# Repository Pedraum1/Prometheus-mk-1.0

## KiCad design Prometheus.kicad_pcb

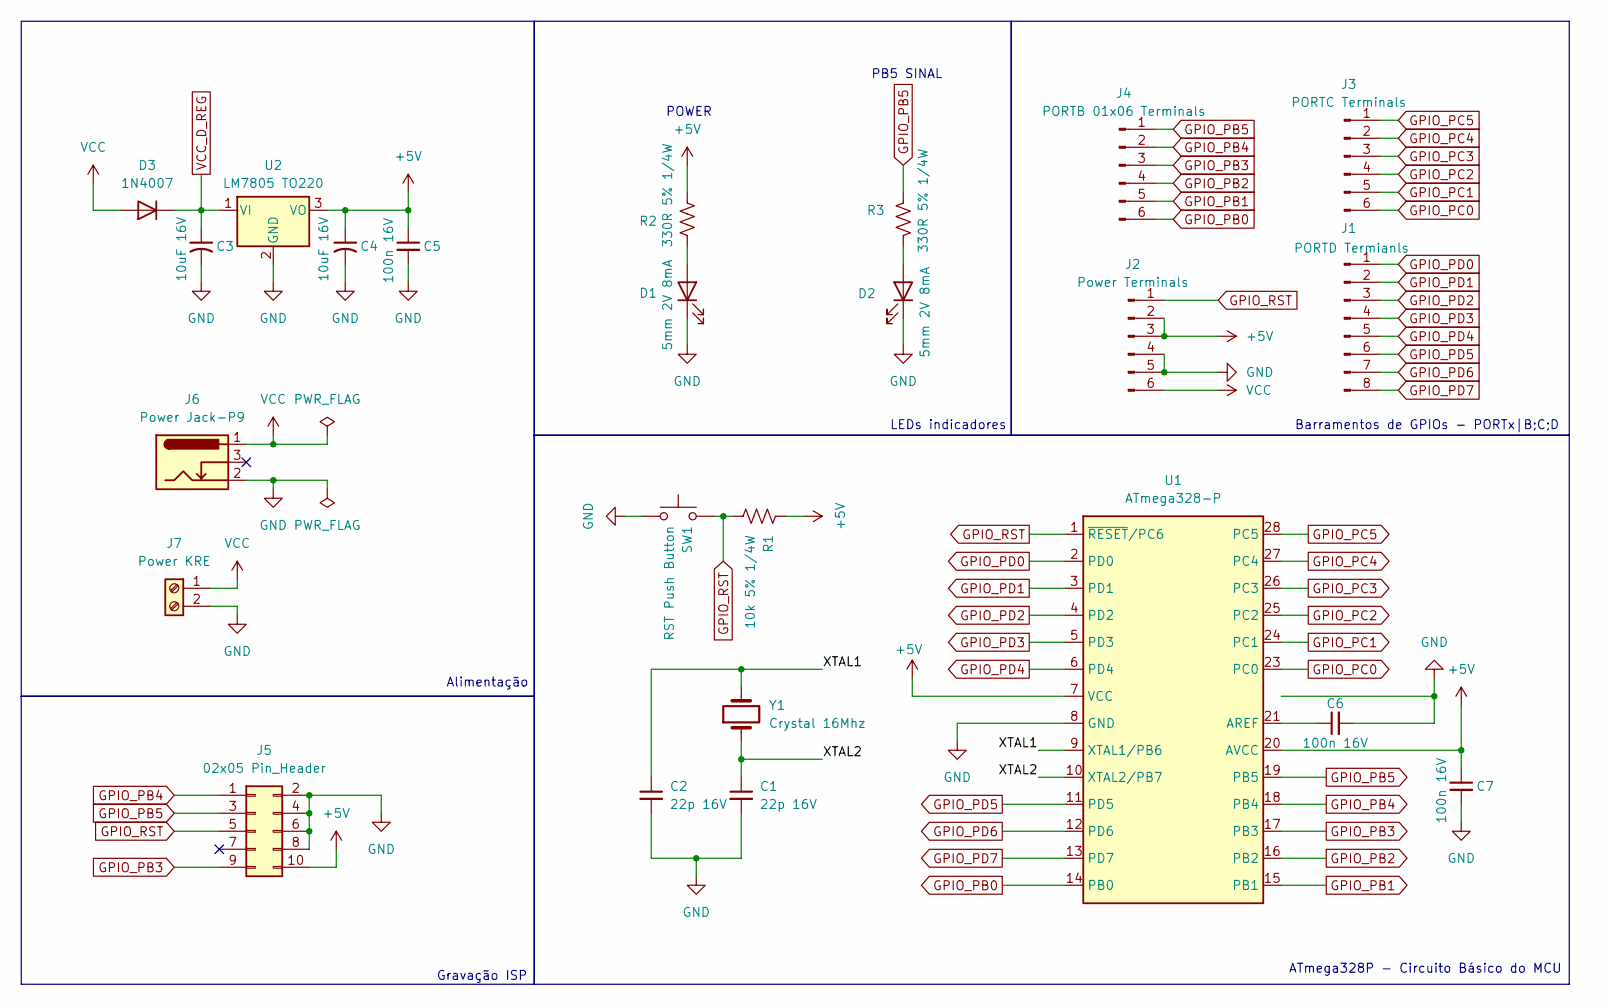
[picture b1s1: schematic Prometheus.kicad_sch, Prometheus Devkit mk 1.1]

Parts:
C1, C2: 22p 16V; C_Disc_D4.7mm_W2.5mm_P5.00mm
C3, C4: 10uF 16V; C_Radial_D5.0mm_H11.0mm_P2.00mm
C5, C6, C7: 100n 16V; C_Disc_D4.7mm_W2.5mm_P5.00mm
D1, D2: 5mm 2V 8mA; LED_D5.0mm
D3: 1N4007; D_DO-41_SOD81_P10.16mm_Horizontal
J1: PORTD Termianls; PinSocket_1x08_P2.54mm_Vertical
J2: Power Terminals; PinSocket_1x06_P2.54mm_Vertical
J3: PORTC Terminals; PinSocket_1x06_P2.54mm_Vertical
J4: PORTB 01x06 Terminals; PinSocket_1x06_P2.54mm_Vertical
J5: 02x05 Pin_Header; IDC-Header_2x05_P2.54mm_Vertical
J6: Power Jack-P9; BarrelJack_Horizontal
J7: Power KRE; TerminalBlock_Phoenix_MKDS-1,5-2-5.08_1x02_P5.08mm_Horizont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
R1: 10k 5% 1/4W; R_Axial_DIN0207_L6.3mm_D2.5mm_P7.62mm_Horizontal
R2, R3: 330R 5% 1/4W; R_Axial_DIN0207_L6.3mm_D2.5mm_P7.62mm_Horizontal
SW1: RST Push Button; SW_PUSH_6mm_H4.3mm
U1: ATmega328-P; DIP-28_W7.62mm_Socket
U2: LM7805 TO220; TO-220-3_Vertical
Y1: Crystal 16Mhz; Crystal_HC49-U_Vertical

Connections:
+5V: C4.1, C5.1, C7.1, J2.2, J2.3, J5.10, R1.1, R2.1, U1.7 (VCC), U1.20 (AVCC), U2.3 (VO)
/XTAL1: C2.1, U1.9 (XTAL1/PB6), Y1.2
/XTAL2: C1.1, U1.10 (XTAL2/PB7), Y1.1
GND: C1.2, C2.2, C3.2, C4.2, C5.2, C6.2, C7.2, D1.1 (K), D2.1 (K), J2.4, J2.5, J5.2, J5.4, J5.6, J5.8, J6.2, J7.2, SW1.1, U1.8 (GND), U1.22 (GND), U2.2 (GND)
GPIO_PB0: J4.6, U1.14 (PB0)
GPIO_PB1: J4.5, U1.15 (PB1)
GPIO_PB2: J4.4, U1.16 (PB2)
GPIO_PB3: J4.3, J5.9, U1.17 (PB3)
GPIO_PB4: J4.2, J5.1, U1.18 (PB4)
GPIO_PB5: J4.1, J5.3, R3.1, U1.19 (PB5)
GPIO_PC0: J3.6, U1.23 (PC0)
GPIO_PC1: J3.5, U1.24 (PC1)
GPIO_PC2: J3.4, U1.25 (PC2)
GPIO_PC3: J3.3, U1.26 (PC3)
GPIO_PC4: J3.2, U1.27 (PC4)
GPIO_PC5: J3.1, U1.28 (PC5)
GPIO_PD0: J1.1, U1.2 (PD0)
GPIO_PD1: J1.2, U1.3 (PD1)
GPIO_PD2: J1.3, U1.4 (PD2)
GPIO_PD3: J1.4, U1.5 (PD3)
GPIO_PD4: J1.5, U1.6 (PD4)
GPIO_PD5: J1.6, U1.11 (PD5)
GPIO_PD6: J1.7, U1.12 (PD6)
GPIO_PD7: J1.8, U1.13 (PD7)
GPIO_RST: J2.1, J5.5, R1.2, SW1.2, U1.1 (~RESET/PC6)
unnamed: D1.2 (A), R2.2
unnamed: D2.2 (A), R3.2
unnamed: C6.1, U1.21 (AREF)
VCC: D3.2 (A), J2.6, J6.1, J7.1
VCC_D_REG: C3.1, D3.1 (K), U2.1 (VI)

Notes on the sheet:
PB5 SINAL
LEDs indicadores
POWER
Alimentação
Gravação ISP
ATmega328P - Circuito Básico do MCU
Barramentos de GPIOs - PORTx|B;C;D

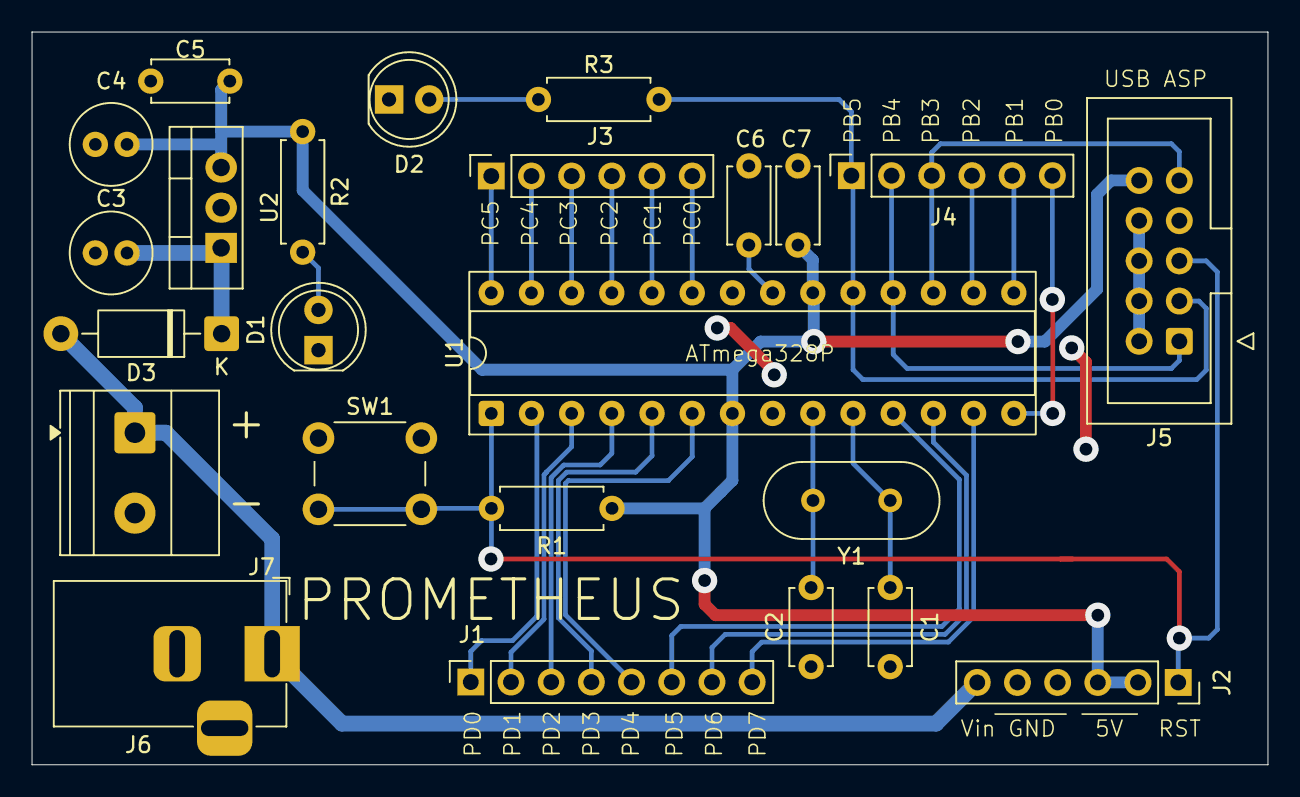
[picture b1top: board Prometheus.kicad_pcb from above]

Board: 2 copper layers, 78.1 x 46.3 mm, 24 parts (0 on the bottom side), 30 nets.

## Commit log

2025-11-29 Criando repositório: Prometheus mk 1.0
